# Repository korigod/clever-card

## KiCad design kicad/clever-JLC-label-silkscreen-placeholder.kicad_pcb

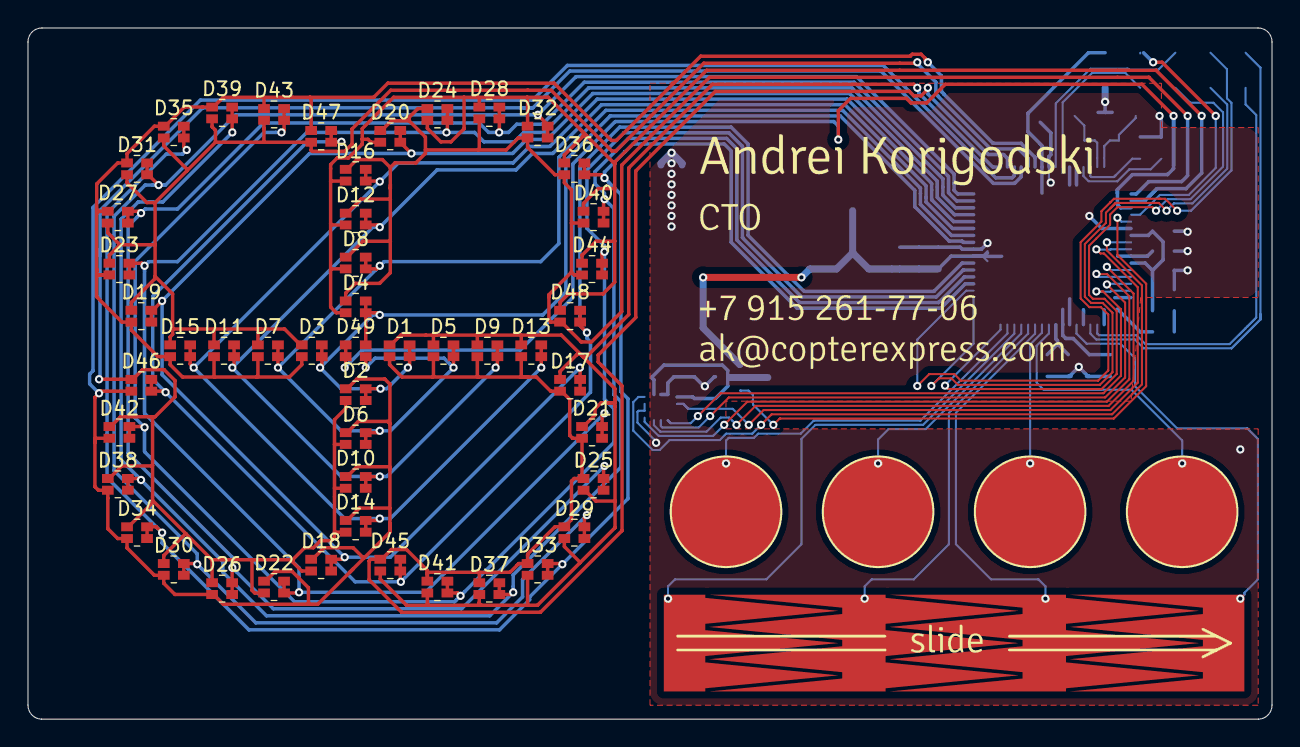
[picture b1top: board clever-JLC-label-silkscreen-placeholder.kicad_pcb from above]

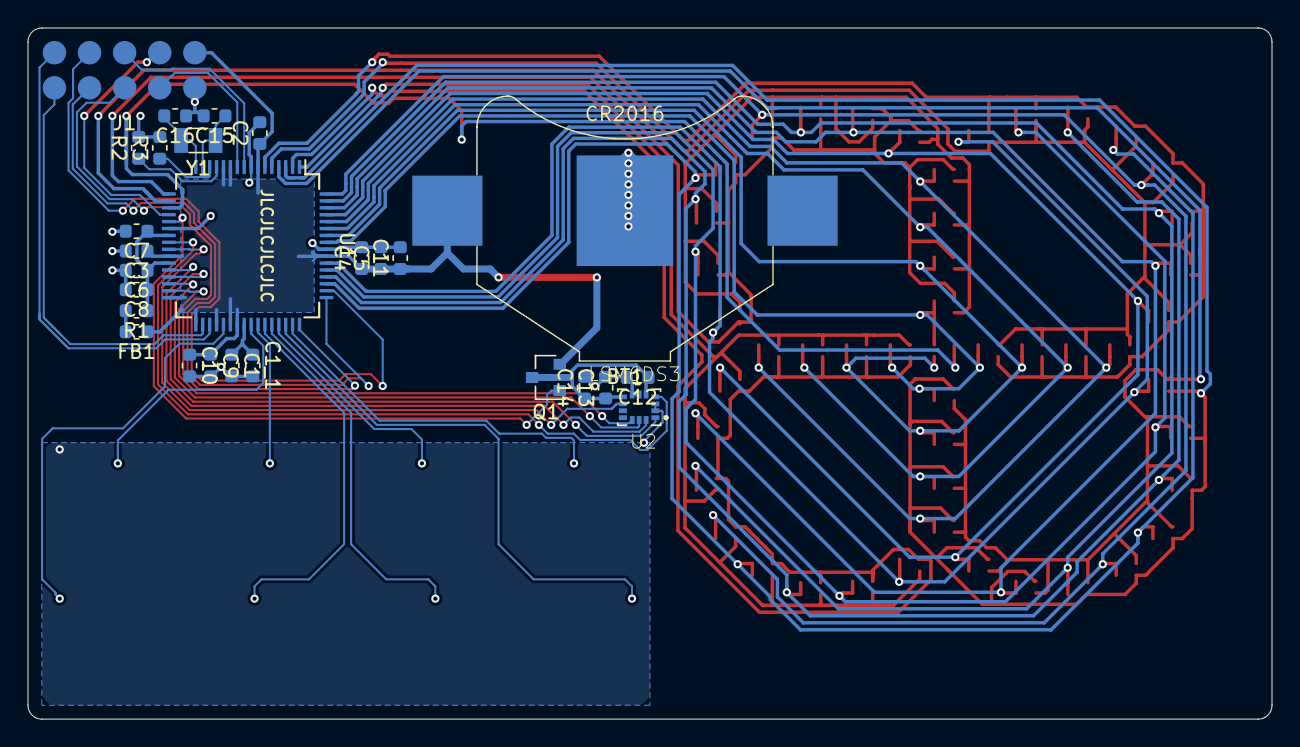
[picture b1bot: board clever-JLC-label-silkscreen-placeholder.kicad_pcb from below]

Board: 2 copper layers, 90.0 x 50.0 mm, 85 parts (27 on the bottom side), 54 nets.

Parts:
BT1: Battery_Cell; BatteryHolder_Keystone_3026_1x2016
C1, C5: 1uF; C_0603_1608Metric
C1_1, C8, C10, C14: 10uF; C_0603_1608Metric
C2, C3, C4, C9, C12, C13: 0.1uF; C_0603_1608Metric
C6, C7: 10nF; C_0603_1608Metric
C11: 47uF; C_0603_1608Metric
C15, C16: 22pF; C_0603_1608Metric
D1, D2, D3, D4, D5, D6, D7, D8, D9, D10, D11, D12, D13, D14, D15, D16, D17, D18, D19, D20, D21, D22, D23, D24, D25, D26, D27, D28, D29, D30, D31, D32, D33, D34, D35, D36, D37, D38, D39, D40, D41, D42, D43, D44, D45, D46, D47, D48, D49: LED_Dual_AACC; LED_DUAL_0606
FB1: Ferrite_Bead_Small; L_0603_1608Metric
J1: POGO_10PADS; TestPoints_2x05_P2.54_D1.7
Q1: Q_PMOS_GSD; SOT-23
R1: 1; R_0603_1608Metric
R2, R3: 0; R_0603_1608Metric
TS1, TS2, TS3, TS4: TOUCH_PAD; TouchPad_D8.0mm
TS5: TOUCH_SLIDER_4PADS; TouchSlider-4_42x7mm
U1: EFM32LG232F64; LQFP-64_10x10mm_P0.5mm
U2: LSM6DS3
Y1: 32768Hz; Crystal_SMD_3215-2Pin_3.2x1.5mm
svg2mod: G***; Text_Slide_Signika_Cu
svg2mod#2: G***; Text_Position_SilkS
svg2mod#3: G***; Text_Contacts_Reversed-2_SilkS
svg2mod#4: G***; Text_Name_without-i-dot_9.5pt_SilkS

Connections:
GND: BT1.2, C1.2, C1_1.2, C2.2, C3.2, C4.2, C5.2, C6.2, C7.2, C8.2, C9.2, C10.2, C11.2, C12.2, C13.2, C14.2, C15.2, C16.2, J1.2, R2.2, R3.2, U1.8, U1.22, U1.56, U2.2, U2.3, U2.6, U2.7
IMU_VDD: C12.1, C13.1, C14.1, Q1.3, U2.5, U2.8
LED_A0: D1.1, D5.1, D9.1, D13.1, D17.1, D21.1, D25.2, D29.2, D33.2, D37.2, D41.2, D45.2, U1.1
LED_A1: D1.2, D5.2, D9.2, D13.2, D17.2, D21.2, D25.1, D29.1, D33.1, D37.1, D41.1, D45.1, U1.2
LED_A2: D2.1, D6.1, D10.1, D14.1, D18.1, D22.1, D26.2, D30.2, D34.2, D38.2, D42.2, D46.2, U1.3
LED_A3: D2.2, D6.2, D10.2, D14.2, D18.2, D22.2, D26.1, D30.1, D34.1, D38.1, D42.1, D46.1, U1.4
LED_A4: D3.1, D7.1, D11.1, D15.1, D19.1, D23.1, D27.2, D31.2, D35.2, D39.2, D43.2, D47.2, U1.5
LED_A5: D3.2, D7.2, D11.2, D15.2, D19.2, D23.2, D27.1, D31.1, D35.1, D39.1, D43.1, D47.1, U1.6
LED_A6: D4.1, D8.1, D12.1, D16.1, D20.1, D24.1, D28.2, D32.2, D36.2, D40.2, D44.2, D48.2, U1.17
LED_A7: D4.2, D8.2, D12.2, D16.2, D20.2, D24.2, D28.1, D32.1, D36.1, D40.1, D44.1, D48.1, U1.18
LED_A8: D49.1, D49.2, U1.19
LED_K0: D1.3, D1.4, D2.3, D2.4, D3.3, D3.4, D4.3, D4.4, D49.3, U1.57
LED_K1: D5.3, D5.4, D6.3, D6.4, D7.3, D7.4, D8.3, D8.4, D49.4, U1.58
LED_K2: D9.3, D9.4, D10.3, D10.4, D11.3, D11.4, D12.3, D12.4, U1.59
LED_K3: D13.3, D13.4, D14.3, D14.4, D15.3, D15.4, D16.3, D16.4, U1.60
LED_K4: D17.3, D17.4, D18.3, D18.4, D19.3, D19.4, D20.3, D20.4, U1.61
LED_K5: D21.3, D21.4, D22.3, D22.4, D23.3, D23.4, D24.3, D24.4, U1.62
LED_K6: D25.3, D25.4, D26.3, D26.4, D27.3, D27.4, D28.3, D28.4, U1.63
LED_K7: D29.3, D29.4, D30.3, D30.4, D31.3, D31.4, D32.3, D32.4, U1.64
LED_K8: D33.3, D33.4, D34.3, D34.4, D35.3, D35.4, D36.3, D36.4, U1.51
LED_K9: D37.3, D37.4, D38.3, D38.4, D39.3, D39.4, D40.3, D40.4, U1.52
LED_K10: D41.3, D41.4, D42.3, D42.4, D43.3, D43.4, D44.3, D44.4, U1.53
LED_K11: D45.3, D45.4, D46.3, D46.4, D47.3, D47.4, D48.3, D48.4, U1.54
LFXTAL_N: C16.1, U1.16, Y1.2
LFXTAL_P: C15.1, U1.15, Y1.1
MCU_AVDD: C6.1, C7.1, C8.1, R1.2, U1.23, U1.27
unnamed: C1.1, C1_1.1, U1.40
unnamed: FB1.2, R1.1
unnamed: J1.3, U1.20
unnamed: J1.4, U1.10
unnamed: J1.5, U1.9
unnamed: J1.6, U1.48
unnamed: J1.7, U1.50
unnamed: J1.8, U1.49
unnamed: J1.9, U1.35
unnamed: J1.10, U1.34
unnamed: Q1.1, U1.21
unnamed: U1.29, U2.1
unnamed: U1.28, U2.14
unnamed: U1.30, U2.13
unnamed: U1.31, U2.12
unnamed: U1.24, U2.4
unnamed: U1.25, U2.9
unnamed: TS5.1, U1.46
unnamed: TS5.2, U1.44
unnamed: TS5.3, U1.43
unnamed: TS5.4, U1.37
unnamed: R2.1, U1.13
unnamed: R3.1, U1.14
TOUCH_PAD0: TS1.1, U1.47
TOUCH_PAD1: TS2.1, U1.45
TOUCH_PAD2: TS3.1, U1.42
TOUCH_PAD3: TS4.1, U1.41
VDD: BT1.1, C2.1, C3.1, C4.1, C5.1, C9.1, C10.1, C11.1, FB1.1, J1.1, Q1.2, U1.7, U1.11, U1.12, U1.26, U1.32, U1.33, U1.36, U1.38, U1.39, U1.55

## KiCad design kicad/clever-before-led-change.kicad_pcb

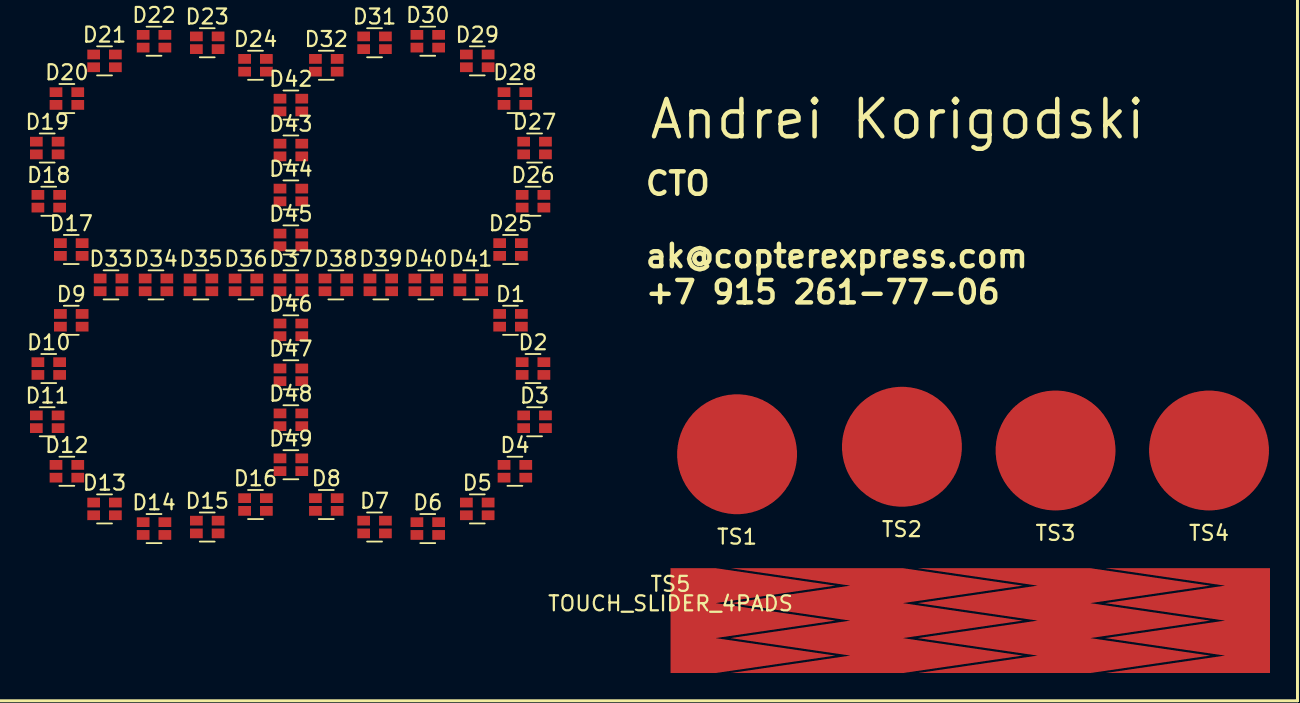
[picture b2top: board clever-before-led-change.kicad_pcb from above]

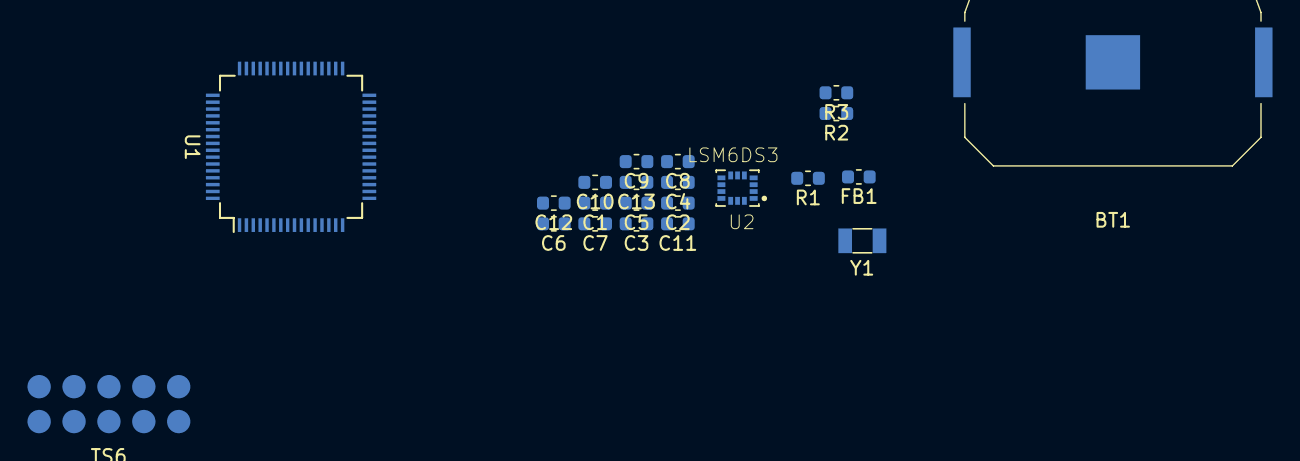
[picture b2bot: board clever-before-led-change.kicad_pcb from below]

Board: 2 copper layers, 76 parts (22 on the bottom side), 52 nets, no tracks yet.

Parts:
BT1: Battery_Cell; BatteryHolder_Keystone_3034_1x20mm
C1: 1uF; C_0603_1608Metric
C2, C3, C4, C9, C12, C13: 0.1uF; C_0603_1608Metric
C5, C8: 10uF; C_0603_1608Metric
C6, C7: 10nF; C_0603_1608Metric
C10: 3.3uF; C_0603_1608Metric
C11: 100uF; C_0603_1608Metric
D1, D2, D3, D4, D5, D6, D7, D8, D9, D10, D11, D12, D13, D14, D15, D16, D17, D18, D19, D20, D21, D22, D23, D24, D25, D26, D27, D28, D29, D30, D31, D32, D33, D34, D35, D36, D37, D38, D39, D40, D41, D42, D43, D44, D45, D46, D47, D48, D49: LED_Dual_AACC; LED_DUAL_0606
FB1: Ferrite_Bead_Small; L_0603_1608Metric
R1: 1; R_0603_1608Metric
R2, R3: 0; R_0603_1608Metric
TS1, TS2, TS3, TS4: TOUCH_PAD; TouchPad_D8.0mm
TS5: TOUCH_SLIDER_4PADS; TouchSlider-4_50x8mm
TS6: POGO_10PADS; TestPoints_2x05_P2.54_D1.7
U1: EFM32LG232F64; LQFP-64_10x10mm_P0.5mm
U2: LSM6DS3
Y1: 32768Hz; Crystal_SMD_3215-2Pin_3.2x1.5mm

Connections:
GND: BT1.2, C1.2, C2.2, C3.2, C4.2, C5.2, C6.2, C7.2, C8.2, C9.2, C10.2, C11.2, C12.2, C13.2, R2.2, R3.2, TS6.2, U1.8, U1.11, U1.12, U1.21, U1.22, U1.32, U1.33, U1.36, U1.38, U1.56, U2.2, U2.3, U2.6, U2.7
LED_A0: D1.1, D1.2, D2.1, D2.2, D3.1, D3.2, D4.1, D4.2, D5.1, D5.2, D6.1, D6.2, U1.1
LED_A1: D7.1, D7.2, D8.1, D8.2, D9.1, D9.2, D10.1, D10.2, D11.1, D11.2, D12.1, D12.2, U1.2
LED_A2: D13.1, D13.2, D14.1, D14.2, D15.1, D15.2, D16.1, D16.2, D17.1, D17.2, D18.1, D18.2, U1.3
LED_A3: D19.1, D19.2, D20.1, D20.2, D21.1, D21.2, D22.1, D22.2, D23.1, D23.2, D24.1, D24.2, U1.4
LED_A4: D25.1, D25.2, D26.1, D26.2, D27.1, D27.2, D28.1, D28.2, D29.1, D29.2, D30.1, D30.2, U1.5
LED_A5: D31.1, D31.2, D32.1, D32.2, D33.1, D33.2, D34.1, D34.2, D35.1, D35.2, D36.1, D36.2, U1.6
LED_A6: D37.1, D37.2, D38.1, D38.2, D39.1, D39.2, D40.1, D40.2, D41.1, D41.2, D42.1, D42.2, U1.17
LED_A7: D43.1, D43.2, D44.1, D44.2, D45.1, D45.2, D46.1, D46.2, D47.1, D47.2, D48.1, D48.2, U1.18
LED_A8: D49.1, D49.2, U1.19
LED_K0: D1.3, D7.3, D13.3, D19.3, D25.3, D31.3, D37.3, D43.3, D49.3, U1.51
LED_K1: D1.4, D7.4, D13.4, D19.4, D25.4, D31.4, D37.4, D43.4, D49.4, U1.52
LED_K2: D2.3, D8.3, D14.3, D20.3, D26.3, D32.3, D38.3, D44.3, U1.53
LED_K3: D2.4, D8.4, D14.4, D20.4, D26.4, D32.4, D38.4, D44.4, U1.54
LED_K4: D3.3, D9.3, D15.3, D21.3, D27.3, D33.3, D39.3, D45.3, U1.57
LED_K5: D3.4, D9.4, D15.4, D21.4, D27.4, D33.4, D39.4, D45.4, U1.58
LED_K6: D4.3, D10.3, D16.3, D22.3, D28.3, D34.3, D40.3, D46.3, U1.59
LED_K7: D4.4, D10.4, D16.4, D22.4, D28.4, D34.4, D40.4, D46.4, U1.60
LED_K8: D5.3, D11.3, D17.3, D23.3, D29.3, D35.3, D41.3, D47.3, U1.61
LED_K9: D5.4, D11.4, D17.4, D23.4, D29.4, D35.4, D41.4, D47.4, U1.62
LED_K10: D6.3, D12.3, D18.3, D24.3, D30.3, D36.3, D42.3, D48.3, U1.63
LED_K11: D6.4, D12.4, D18.4, D24.4, D30.4, D36.4, D42.4, D48.4, U1.64
MCU_AVDD: C6.1, C7.1, C8.1, R1.2, U1.23, U1.27
unnamed: C1.1, U1.40
unnamed: FB1.2, R1.1
unnamed: TS6.3, U1.20
unnamed: TS6.4, U1.10
unnamed: TS6.5, U1.9
unnamed: TS6.6, U1.48
unnamed: TS6.7, U1.50
unnamed: TS6.8, U1.49
unnamed: TS6.9, U1.35
unnamed: TS6.10, U1.34
unnamed: U1.15, Y1.1
unnamed: U1.16, Y1.2
unnamed: U1.29, U2.1
unnamed: U1.28, U2.14
unnamed: U1.30, U2.13
unnamed: U1.31, U2.12
unnamed: U1.24, U2.4
unnamed: U1.25, U2.9
unnamed: TS5.1, U1.44
unnamed: TS5.2, U1.45
unnamed: TS5.3, U1.46
unnamed: TS5.4, U1.47
unnamed: R2.1, U1.13
unnamed: R3.1, U1.14
TOUCH_PAD0: TS1.1, U1.37
TOUCH_PAD1: TS2.1, U1.41
TOUCH_PAD2: TS3.1, U1.42
TOUCH_PAD3: TS4.1, U1.43
VDD: BT1.1, C2.1, C3.1, C4.1, C5.1, C9.1, C10.1, C11.1, C12.1, C13.1, FB1.1, TS6.1, U1.7, U1.26, U1.39, U1.55, U2.5, U2.8
